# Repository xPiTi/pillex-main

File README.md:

# Pillex

Submission files for MSc project - Pillex - pill dispensing device

Read more at: https://paw3l.com/projects/pillex/

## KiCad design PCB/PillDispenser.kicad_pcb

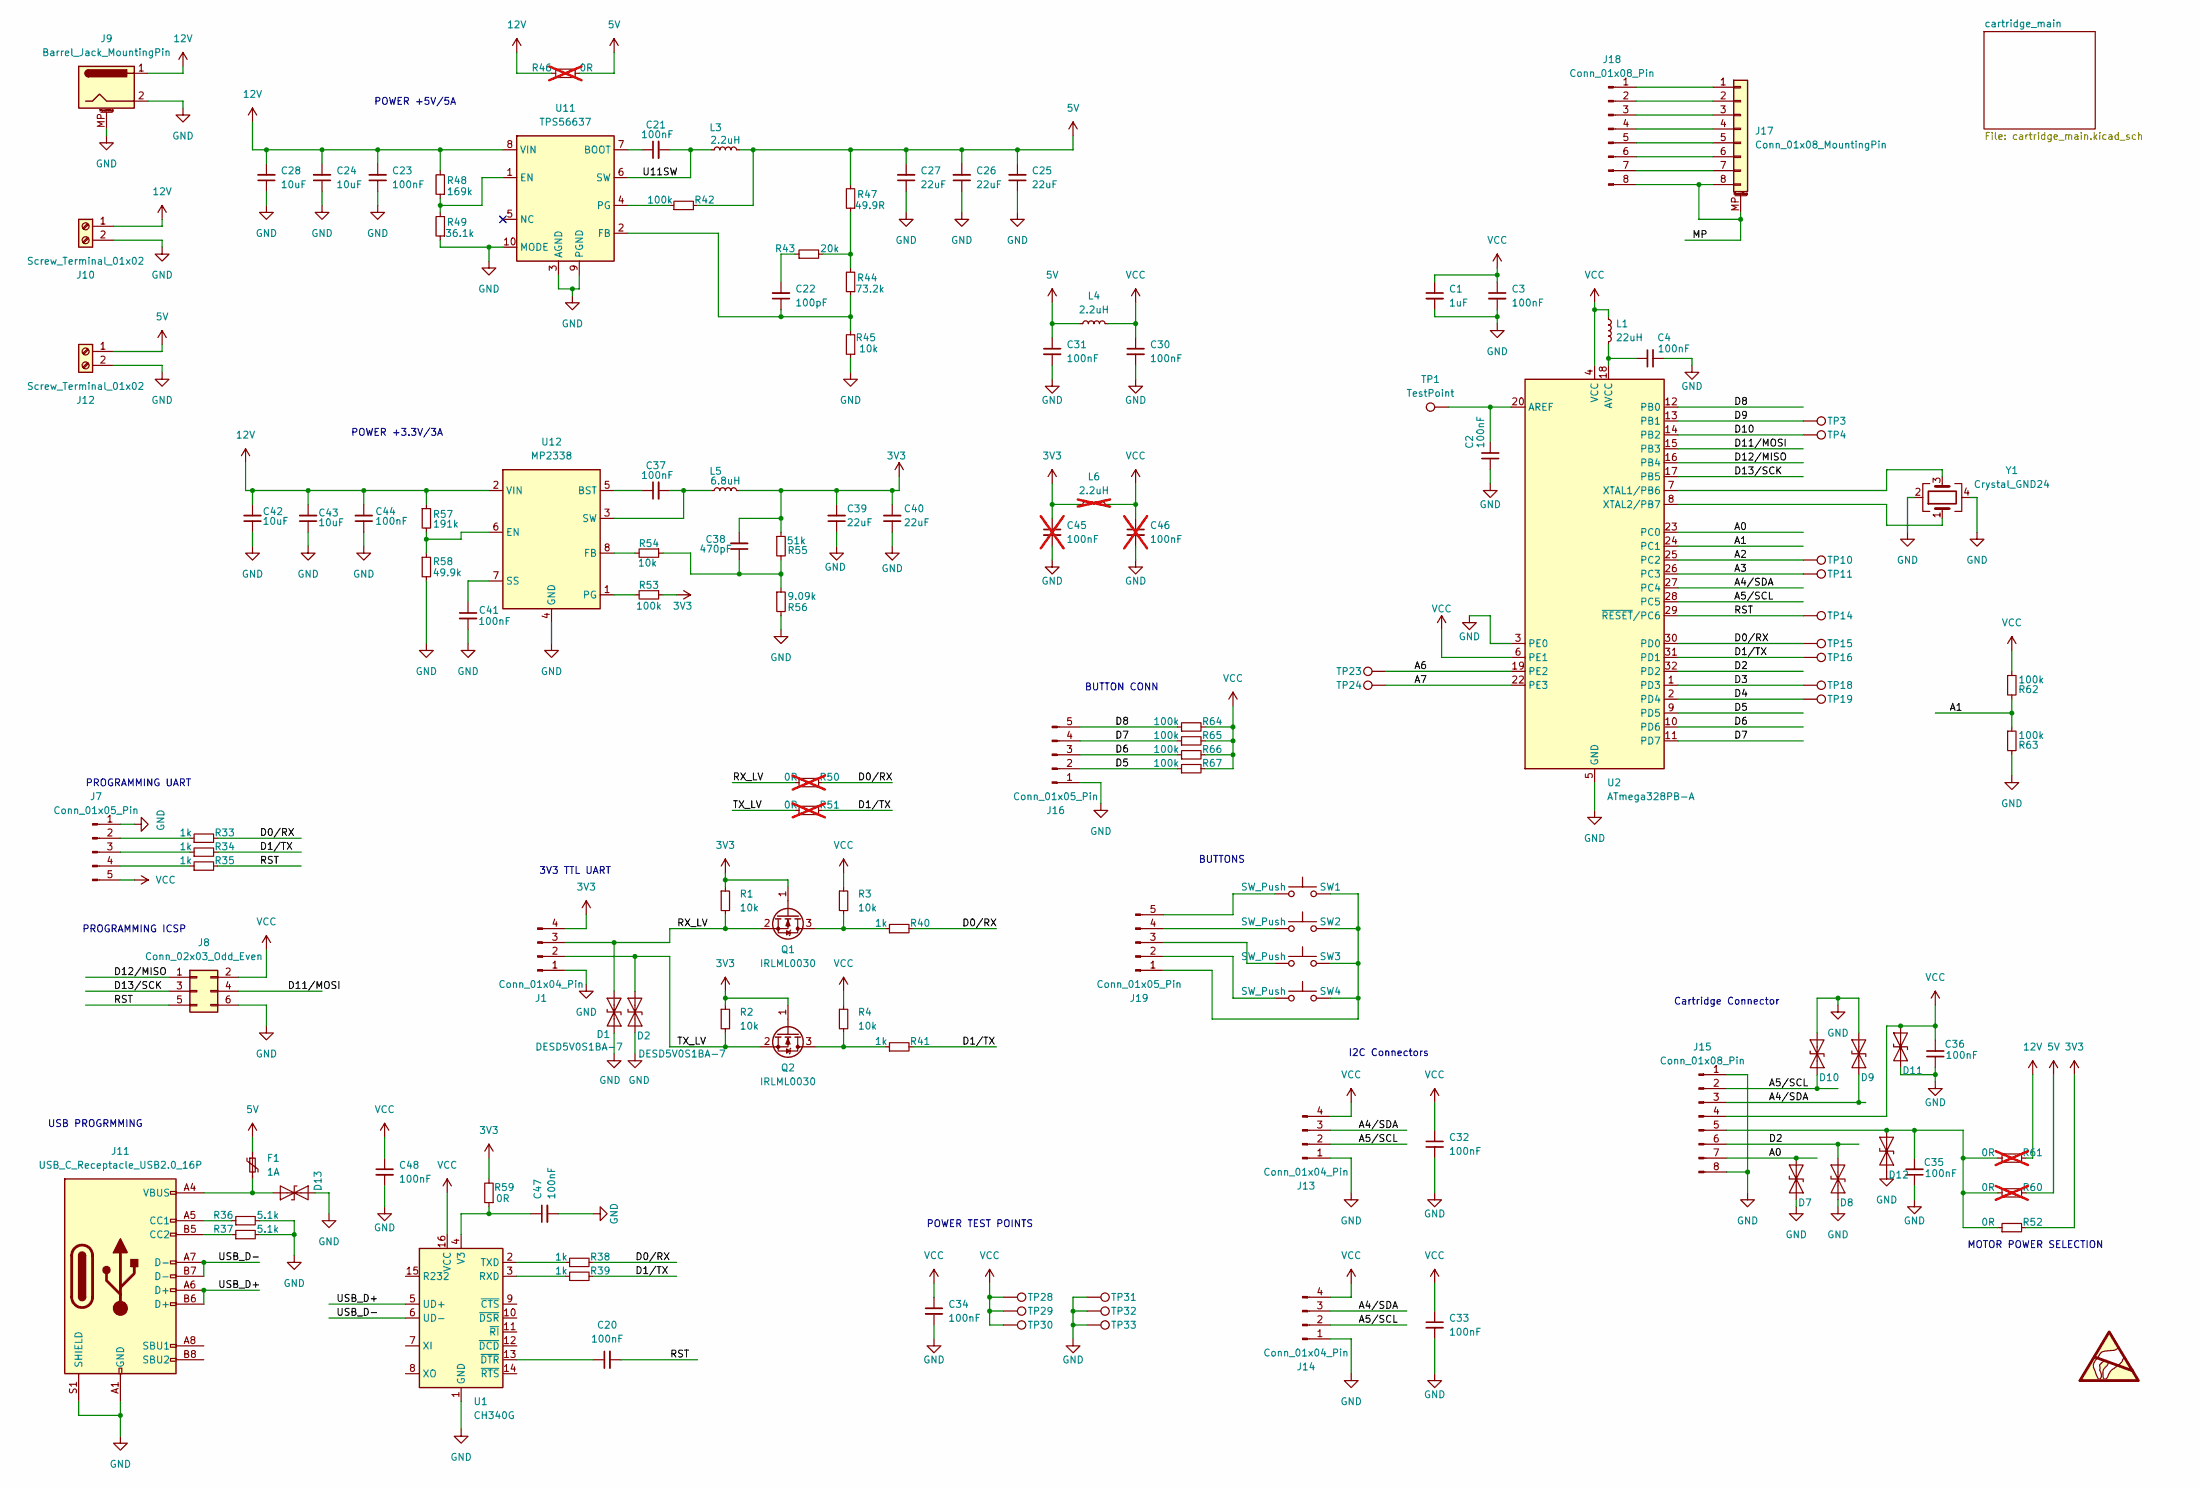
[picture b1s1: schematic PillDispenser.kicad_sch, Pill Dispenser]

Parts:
C1: 1uF; C_0805_2012Metric_Pad1.18x1.45mm_HandSolder
C2, C3, C4, C20, C21, C23, C30, C31, C32, C33, C34, C35, C36, C37, C41, C44, C47, C48: 100nF; C_0805_2012Metric_Pad1.18x1.45mm_HandSolder
C22: 100pF; C_0805_2012Metric_Pad1.18x1.45mm_HandSolder
C24, C28, C42, C43: 10uF; C_0805_2012Metric_Pad1.18x1.45mm_HandSolder
C25, C26, C27, C39, C40: 22uF; C_1206_3216Metric_Pad1.33x1.80mm_HandSolder
C38: 470pF; C_0805_2012Metric_Pad1.18x1.45mm_HandSolder
C45, C46: 100nF; C_0805_2012Metric_Pad1.18x1.45mm_HandSolder; not fitted
D1, D2, D7, D8, D9, D10, D11, D12, D13: DESD5V0S1BA-7; D_SOD-323
F1: 1A; D_1206_3216Metric_Pad1.42x1.75mm_HandSolder
J1, J13, J14: Conn_01x04_Pin; PinHeader_1x04_P2.54mm_Vertical
J7, J16, J19: Conn_01x05_Pin; PinHeader_1x05_P2.54mm_Vertical
J8: Conn_02x03_Odd_Even; PinHeader_2x03_P2.54mm_Vertical
J9: Barrel_Jack_MountingPin; BarrelJack_CUI_PJ-063AH_Horizontal
J10, J12: Screw_Terminal_01x02; Altech_AK100_1x02_P5.00mm
J11: USB_C_Receptacle_USB2.0_16P; USB_C_Receptacle_GCT_USB4085
J15, J18: Conn_01x08_Pin; PinHeader_1x08_P2.54mm_Vertical
J17: Conn_01x08_MountingPin; 009155008852006
L1: 22uH; L_0805_2012Metric_Pad1.15x1.40mm_HandSolder
L3: 2.2uH; L_Coilcraft_XAL4030-XXX
L4: 2.2uH; L_0805_2012Metric_Pad1.15x1.40mm_HandSolder
L5: 6.8uH; L_Coilcraft_XAL4030-XXX
L6: 2.2uH; L_0805_2012Metric_Pad1.15x1.40mm_HandSolder; not fitted
Q1, Q2: IRLML0030; SOT-23
R1, R2, R3, R4, R45, R54: 10k; R_0603_1608Metric_Pad0.98x0.95mm_HandSolder
R33, R34, R35, R38, R39, R40, R41: 1k; R_0603_1608Metric_Pad0.98x0.95mm_HandSolder
R36, R37: 5.1k; R_0603_1608Metric_Pad0.98x0.95mm_HandSolder
R42, R53, R62, R63, R64, R65, R66, R67: 100k; R_0603_1608Metric_Pad0.98x0.95mm_HandSolder
R43: 20k; R_0603_1608Metric_Pad0.98x0.95mm_HandSolder
R44: 73.2k; R_0603_1608Metric_Pad0.98x0.95mm_HandSolder
R46, R50, R51, R60, R61: 0R; R_0603_1608Metric_Pad0.98x0.95mm_HandSolder; not fitted
R47: 49.9R; R_0603_1608Metric_Pad0.98x0.95mm_HandSolder
R48: 169k; R_0603_1608Metric_Pad0.98x0.95mm_HandSolder
R49: 36.1k; R_0603_1608Metric_Pad0.98x0.95mm_HandSolder
R52, R59: 0R; R_0603_1608Metric_Pad0.98x0.95mm_HandSolder
R55: 51k; R_0603_1608Metric_Pad0.98x0.95mm_HandSolder
R56: 9.09k; R_0603_1608Metric_Pad0.98x0.95mm_HandSolder
R57: 191k; R_0603_1608Metric_Pad0.98x0.95mm_HandSolder
R58: 49.9k; R_0603_1608Metric_Pad0.98x0.95mm_HandSolder
SW1, SW2, SW3, SW4: SW_Push; SW_PUSH_6mm_H5mm
TP1, TP3, TP4, TP10, TP11, TP14, TP15, TP16, TP18, TP19, TP23, TP24, TP28, TP29, TP30, TP31, TP32, TP33: TestPoint; TestPoint_Pad_D1.5mm_3D_Model
U1: CH340G; SOIC-16_3.9x9.9mm_P1.27mm
U2: ATmega328PB-A; TQFP-32_7x7mm_P0.8mm
U11: TPS56637; Texas_VQFN-HR_3.1x3.1mm_P1mm_RPA0010A
U12: MP2338; SOT-583-8
Y1: Crystal_GND24; Crystal_SMD_Abracon_ABM8G-4Pin_3.2x2.5mm

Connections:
3V3: C38.2, C39.2, C40.2, C45.1, J1.4, L5.2, L6.1, Q1.1 (G), Q2.1 (G), R1.1, R2.1, R52.2, R53.1, R55.1, R59.2
5V: C25.2, C26.2, C27.2, C31.1, F1.1, J12.1, L3.2, L4.1, R42.2, R46.2, R47.2, R60.2
12V: C23.2, C24.2, C28.2, C42.2, C43.2, C44.2, J9.1, J10.1, R46.1, R48.2, R57.1, R61.2, U11.8 (VIN), U12.2 (VIN)
/A0: D7.2 (A2), J15.7, U2.23 (PC0)
/A1: R62.2, R63.1, U2.24 (PC1)
/A2: TP10.1, U2.25 (PC2)
/A3: TP11.1, U2.26 (PC3)
/A4/SDA: D9.1 (A1), J13.3, J14.3, J15.3, U2.27 (PC4)
/A5/SCL: D10.1 (A1), J13.2, J14.2, J15.2, U2.28 (PC5)
/A6: TP23.1, U2.19 (PE2)
/A7: TP24.1, U2.22 (PE3)
/D0/RX: R33.2, R38.2, R40.2, R50.2, TP15.1, U2.30 (PD0)
/D1/TX: R34.2, R39.2, R41.2, R51.2, TP16.1, U2.31 (PD1)
/D2: D8.2 (A2), J15.6, U2.32 (PD2)
/D3: TP18.1, U2.1 (PD3)
/D4: TP19.1, U2.2 (PD4)
/D5: J16.2, R67.1, U2.9 (PD5)
/D6: J16.3, R66.1, U2.10 (PD6)
/D7: J16.4, R65.1, U2.11 (PD7)
/D8: J16.5, R64.1, U2.12 (PB0)
/D9: TP3.1, U2.13 (PB1)
/D10: TP4.1, U2.14 (PB2)
/D11/MOSI: J8.4, U2.15 (PB3)
/D12/MISO: J8.1, U2.16 (PB4)
/D13/SCK: J8.3, U2.17 (PB5)
/MP: J17.8, J17.MP (MountPin), J18.8
/RST: C20.2, J8.5, R35.2, TP14.1, U2.29 (~RESET/PC6)
/RX_LV: D1.2 (A2), J1.3, Q1.2 (S), R1.2, R50.1
/TX_LV: D2.2 (A2), J1.2, Q2.2 (S), R2.2, R51.1
/U11SW: C21.2, L3.1, U11.6 (SW)
/USB_D+: J11.A6 (D+), J11.B6 (D+), U1.5 (UD+)
/USB_D-: J11.A7 (D-), J11.B7 (D-), U1.6 (UD-)
GND: C1.2, C2.1, C3.2, C4.2, C23.1, C24.1, C25.1, C26.1, C27.1, C28.1, C30.2, C31.2, C32.2, C33.2, C34.2, C35.1, C36.1, C39.1, C40.1, C41.2, C42.1, C43.1, C44.1, C45.2, C46.2, C47.2, C48.2, D1.1 (A1), D2.1 (A1), D7.1 (A1), D8.1 (A1), D9.2 (A2), D10.2 (A2), D11.1 (A1), D12.1 (A1), D13.1 (A1), J1.1, J7.1, J8.6, J9.2, J9.MP (MountPin), J10.2, J11.A1 (GND), J11.A12 (GND), J11.B1 (GND), J11.B12 (GND), J11.S1 (SHIELD), J12.2, J13.1, J14.1, J15.1, J15.8, J16.1, R36.2, R37.2, R45.1, R49.1, R56.2, R58.2, R63.2, TP31.1, TP32.1, TP33.1, U1.1 (GND), U2.3 (PE0), U2.5 (GND), U2.21 (GND), U11.3 (AGND), U11.9 (PGND), U11.10 (MODE), U12.4 (GND), Y1.2, Y1.4
unnamed: C22.2, R43.1
unnamed: C38.1, R54.1, R55.2, R56.1
unnamed: C35.2, D12.2 (A2), J15.5, R52.1, R60.1, R61.1
unnamed: D13.2 (A2), F1.2, J11.A4 (VBUS), J11.A9 (VBUS), J11.B4 (VBUS), J11.B9 (VBUS)
unnamed: J7.2, R33.1
unnamed: J7.3, R34.1
unnamed: J7.4, R35.1
unnamed: J11.A5 (CC1), R36.1
unnamed: J11.B5 (CC2), R37.1
unnamed: J17.1, J18.1
unnamed: J17.2, J18.2
unnamed: J17.3, J18.3
unnamed: J17.4, J18.4
unnamed: J17.5, J18.5
unnamed: J17.6, J18.6
unnamed: J17.7, J18.7
unnamed: J19.1, SW1.2, SW2.2, SW3.2, SW4.2
unnamed: J19.2, SW4.1
unnamed: J19.3, SW3.1
unnamed: J19.4, SW2.1
unnamed: J19.5, SW1.1
unnamed: Q1.3 (D), R3.2, R40.1
unnamed: Q2.3 (D), R4.2, R41.1
unnamed: R43.2, R44.2, R47.1
unnamed: R39.1, U1.3 (RXD)
unnamed: R38.1, U1.2 (TXD)
unnamed: C47.1, R59.1, U1.4 (V3)
unnamed: C20.1, U1.13 (~DTR)
unnamed: C2.2, TP1.1, U2.20 (AREF)
unnamed: C4.1, L1.2, U2.18 (AVCC)
unnamed: U2.7 (XTAL1/PB6), Y1.3
unnamed: U2.8 (XTAL2/PB7), Y1.1
unnamed: C21.1, U11.7 (BOOT)
unnamed: R48.1, R49.2, U11.1 (EN)
unnamed: C22.1, R44.1, R45.2, U11.2 (FB)
unnamed: R42.1, U11.4 (PG)
unnamed: C37.1, U12.5 (BST)
unnamed: R57.2, R58.1, U12.6 (EN)
unnamed: R54.2, U12.8 (FB)
unnamed: R53.2, U12.1 (PG)
unnamed: C41.1, U12.7 (SS)
unnamed: C37.2, L5.1, U12.3 (SW)
VCC: C1.1, C3.1, C30.1, C32.1, C33.1, C34.1, C36.2, C46.1, C48.1, D11.2 (A2), J7.5, J8.2, J13.4, J14.4, J15.4, L1.1, L4.2, L6.2, R3.1, R4.1, R62.1, R64.2, R65.2, R66.2, R67.2, TP28.1, TP29.1, TP30.1, U1.16 (VCC), U2.4 (VCC), U2.6 (PE1)

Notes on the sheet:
PROGRAMMING UART
BUTTON CONN
BUTTONS
I2C Connectors
Cartridge Connector
MOTOR POWER SELECTION
POWER +3.3V/3A
POWER TEST POINTS
USB PROGRMMING
POWER +5V/5A
3V3 TTL UART
PROGRAMMING ICSP

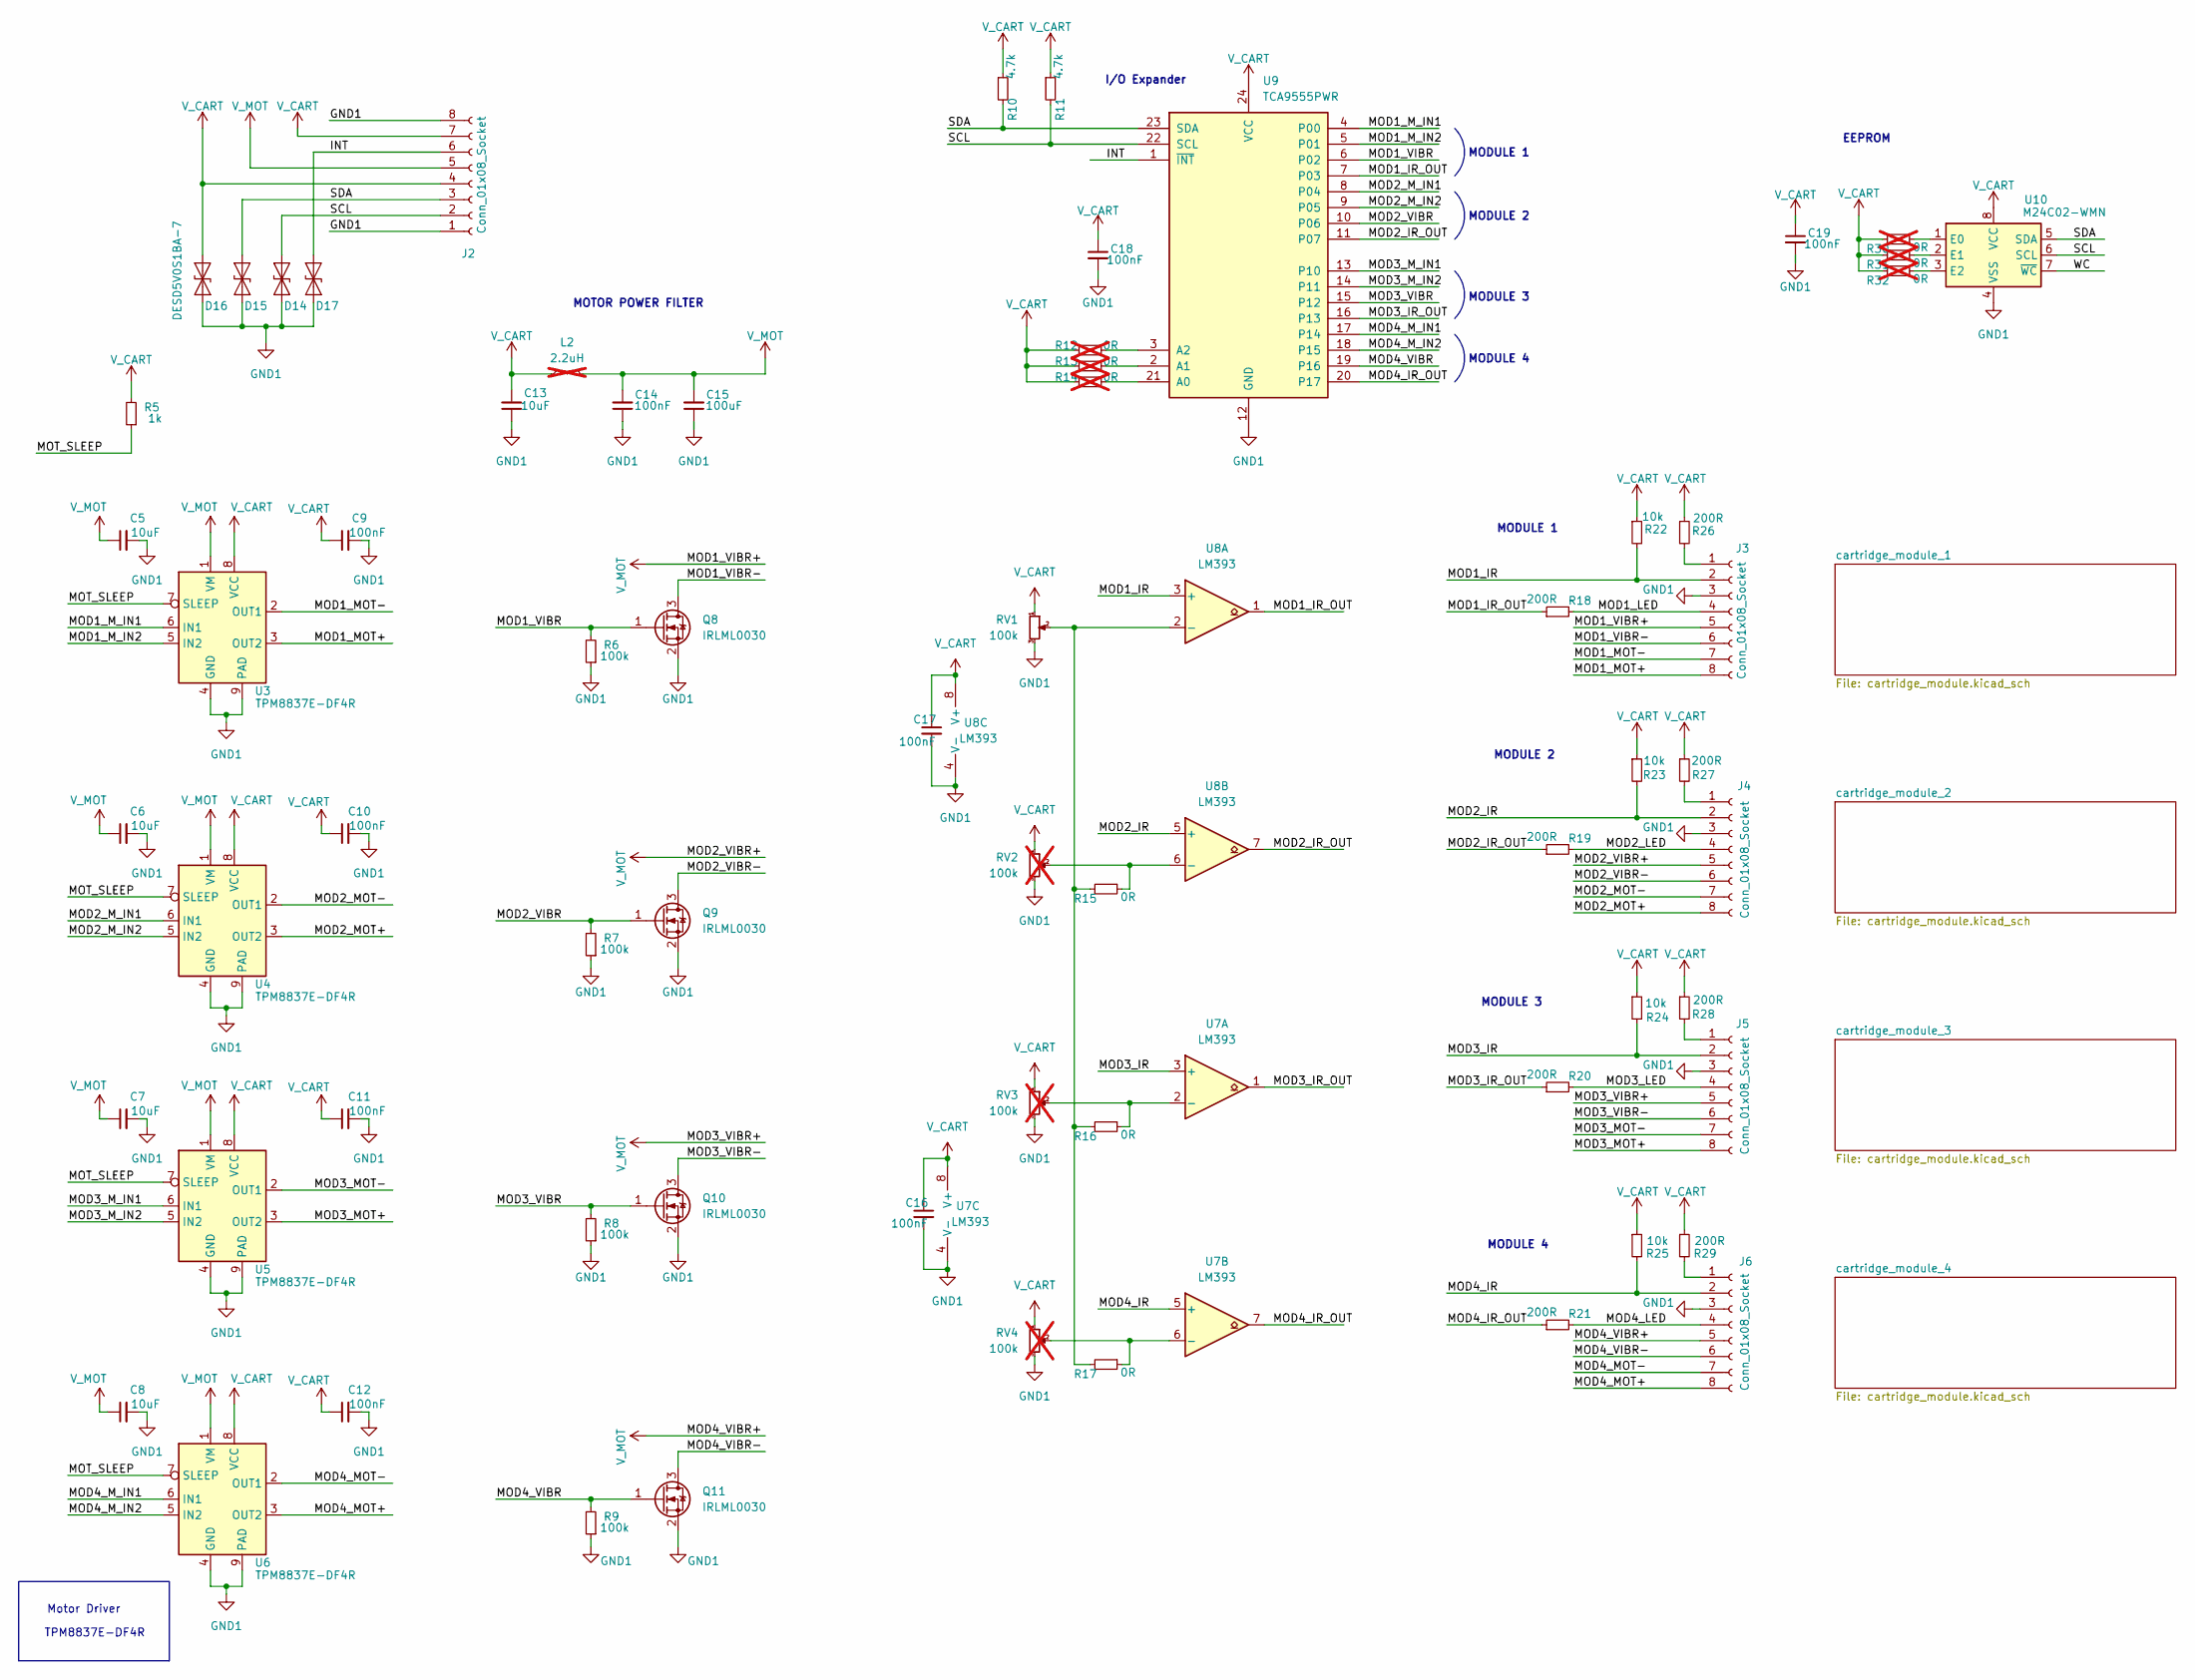
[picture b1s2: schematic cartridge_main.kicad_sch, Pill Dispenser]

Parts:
C5, C6, C7, C8, C13: 10uF; C_0805_2012Metric_Pad1.18x1.45mm_HandSolder
C9, C10, C11, C12, C14, C16, C17, C18, C19: 100nF; C_0805_2012Metric_Pad1.18x1.45mm_HandSolder
C15: 100uF; C_1206_3216Metric_Pad1.33x1.80mm_HandSolder
D14, D15, D16, D17: DESD5V0S1BA-7; D_SOD-323
J2: Conn_01x08_Socket; PCB_Contacts_8pin
J3, J4, J5, J6: Conn_01x08_Socket; PinSocket_1x08_P1.27mm_Vertical
L2: 2.2uH; L_1210_3225Metric_Pad1.42x2.65mm_HandSolder; not fitted
Q8, Q9, Q10, Q11: IRLML0030; SOT-23
R5: 1k; R_0603_1608Metric_Pad0.98x0.95mm_HandSolder
R6, R7, R8, R9: 100k; R_0603_1608Metric_Pad0.98x0.95mm_HandSolder
R10, R11: 4.7k; R_0603_1608Metric_Pad0.98x0.95mm_HandSolder
R12, R13, R14, R30, R31, R32: 0R; R_0603_1608Metric_Pad0.98x0.95mm_HandSolder; not fitted
R15, R16, R17: 0R; R_0603_1608Metric_Pad0.98x0.95mm_HandSolder
R18, R19, R20, R21, R26, R27, R28, R29: 200R; R_0603_1608Metric_Pad0.98x0.95mm_HandSolder
R22, R23, R24, R25: 10k; R_0603_1608Metric_Pad0.98x0.95mm_HandSolder
RV1: 100k; Potentiometer_Bourns_TC33X_Vertical
RV2, RV3, RV4: 100k; Potentiometer_Bourns_TC33X_Vertical; not fitted
U3, U4, U5, U6: TPM8837E-DF4R; DFN-8-1EP_2x2mm_P0.5mm_EP1.05x1.75mm_hand_solder
U7, U8: LM393; SOIC-8_3.9x4.9mm_P1.27mm
U9: TCA9555PWR; TSSOP-24_4.4x7.8mm_P0.65mm
U10: M24C02-WMN; SOIC-8_3.9x4.9mm_P1.27mm

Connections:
/cartridge_main/INT: D17.2 (A2), J2.6, U9.1 (~INT)
/cartridge_main/MOD1_IR: J3.2, R22.2, U8.3 (+)
/cartridge_main/MOD1_IR_OUT: R18.1, U8.1, U9.7 (P03)
/cartridge_main/MOD1_LED: J3.4, R18.2
/cartridge_main/MOD1_MOT+: J3.8, U3.3 (OUT2)
/cartridge_main/MOD1_MOT-: J3.7, U3.2 (OUT1)
/cartridge_main/MOD1_M_IN1: U3.6 (IN1), U9.4 (P00)
/cartridge_main/MOD1_M_IN2: U3.5 (IN2), U9.5 (P01)
/cartridge_main/MOD1_VIBR: Q8.1 (G), R6.2, U9.6 (P02)
/cartridge_main/MOD1_VIBR-: J3.6, Q8.3 (D)
/cartridge_main/MOD2_IR: J4.2, R23.2, U8.5 (+)
/cartridge_main/MOD2_IR_OUT: R19.1, U8.7, U9.11 (P07)
/cartridge_main/MOD2_LED: J4.4, R19.2
/cartridge_main/MOD2_MOT+: J4.8, U4.3 (OUT2)
/cartridge_main/MOD2_MOT-: J4.7, U4.2 (OUT1)
/cartridge_main/MOD2_M_IN1: U4.6 (IN1), U9.8 (P04)
/cartridge_main/MOD2_M_IN2: U4.5 (IN2), U9.9 (P05)
/cartridge_main/MOD2_VIBR: Q9.1 (G), R7.2, U9.10 (P06)
/cartridge_main/MOD2_VIBR-: J4.6, Q9.3 (D)
/cartridge_main/MOD3_IR: J5.2, R24.2, U7.3 (+)
/cartridge_main/MOD3_IR_OUT: R20.1, U7.1, U9.16 (P13)
/cartridge_main/MOD3_LED: J5.4, R20.2
/cartridge_main/MOD3_MOT+: J5.8, U5.3 (OUT2)
/cartridge_main/MOD3_MOT-: J5.7, U5.2 (OUT1)
/cartridge_main/MOD3_M_IN1: U5.6 (IN1), U9.13 (P10)
/cartridge_main/MOD3_M_IN2: U5.5 (IN2), U9.14 (P11)
/cartridge_main/MOD3_VIBR: Q10.1 (G), R8.2, U9.15 (P12)
/cartridge_main/MOD3_VIBR-: J5.6, Q10.3 (D)
/cartridge_main/MOD4_IR: J6.2, R25.2, U7.5 (+)
/cartridge_main/MOD4_IR_OUT: R21.1, U7.7, U9.20 (P17)
/cartridge_main/MOD4_LED: J6.4, R21.2
/cartridge_main/MOD4_MOT+: J6.8, U6.3 (OUT2)
/cartridge_main/MOD4_MOT-: J6.7, U6.2 (OUT1)
/cartridge_main/MOD4_M_IN1: U6.6 (IN1), U9.17 (P14)
/cartridge_main/MOD4_M_IN2: U6.5 (IN2), U9.18 (P15)
/cartridge_main/MOD4_VIBR: Q11.1 (G), R9.2, U9.19 (P16)
/cartridge_main/MOD4_VIBR-: J6.6, Q11.3 (D)
/cartridge_main/MOT_SLEEP: R5.1, U3.7 (SLEEP), U4.7 (SLEEP), U5.7 (SLEEP), U6.7 (SLEEP)
/cartridge_main/SCL: D14.2 (A2), J2.2, R11.2, U9.22 (SCL), U10.6 (SCL)
/cartridge_main/SDA: D15.2 (A2), J2.3, R10.2, U9.23 (SDA), U10.5 (SDA)
/cartridge_main/WC: U10.7 (~WC)
GND1: C5.2, C6.2, C7.2, C8.2, C9.2, C10.2, C11.2, C12.2, C13.1, C14.1, C15.1, C16.2, C17.2, C18.2, C19.2, D14.1 (A1), D15.1 (A1), D16.1 (A1), D17.1 (A1), J2.1, J2.8, J3.3, J4.3, J5.3, J6.3, Q8.2 (S), Q9.2 (S), Q10.2 (S), Q11.2 (S), R6.1, R7.1, R8.1, R9.1, RV1.3, RV2.3, RV3.3, RV4.3, U3.4 (GND), U3.9 (PAD), U4.4 (GND), U4.9 (PAD), U5.4 (GND), U5.9 (PAD), U6.4 (GND), U6.9 (PAD), U7.4 (V-), U8.4 (V-), U9.12 (GND), U10.4 (VSS)
unnamed: J3.1, R26.2
unnamed: J4.1, R27.2
unnamed: J5.1, R28.2
unnamed: J6.1, R29.2
unnamed: R16.1, RV3.2, U7.2 (-)
unnamed: R17.1, RV4.2, U7.6 (-)
unnamed: R15.2, R16.2, R17.2, RV1.2, U8.2 (-)
unnamed: R15.1, RV2.2, U8.6 (-)
unnamed: R14.1, U9.21 (A0)
unnamed: R13.1, U9.2 (A1)
unnamed: R12.1, U9.3 (A2)
unnamed: R30.1, U10.1 (E0)
unnamed: R31.1, U10.2 (E1)
unnamed: R32.1, U10.3 (E2)
V_CART: C9.1, C10.1, C11.1, C12.1, C13.2, C16.1, C17.1, C18.1, C19.1, D16.2 (A2), J2.4, J2.7, L2.1, R5.2, R10.1, R11.1, R12.2, R13.2, R14.2, R22.1, R23.1, R24.1, R25.1, R26.1, R27.1, R28.1, R29.1, R30.2, R31.2, R32.2, RV1.1, RV2.1, RV3.1, RV4.1, U3.8 (VCC), U4.8 (VCC), U5.8 (VCC), U6.8 (VCC), U7.8 (V+), U8.8 (V+), U9.24 (VCC), U10.8 (VCC)
V_MOT: C5.1, C6.1, C7.1, C8.1, C14.2, C15.2, J2.5, J3.5, J4.5, J5.5, J6.5, L2.2, U3.1 (VM), U4.1 (VM), U5.1 (VM), U6.1 (VM)

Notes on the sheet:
Motor Driver
MODULE 1
TPM8837E-DF4R
MODULE 3
MOTOR POWER FILTER
I/O Expander
MODULE 4
MODULE 2
EEPROM

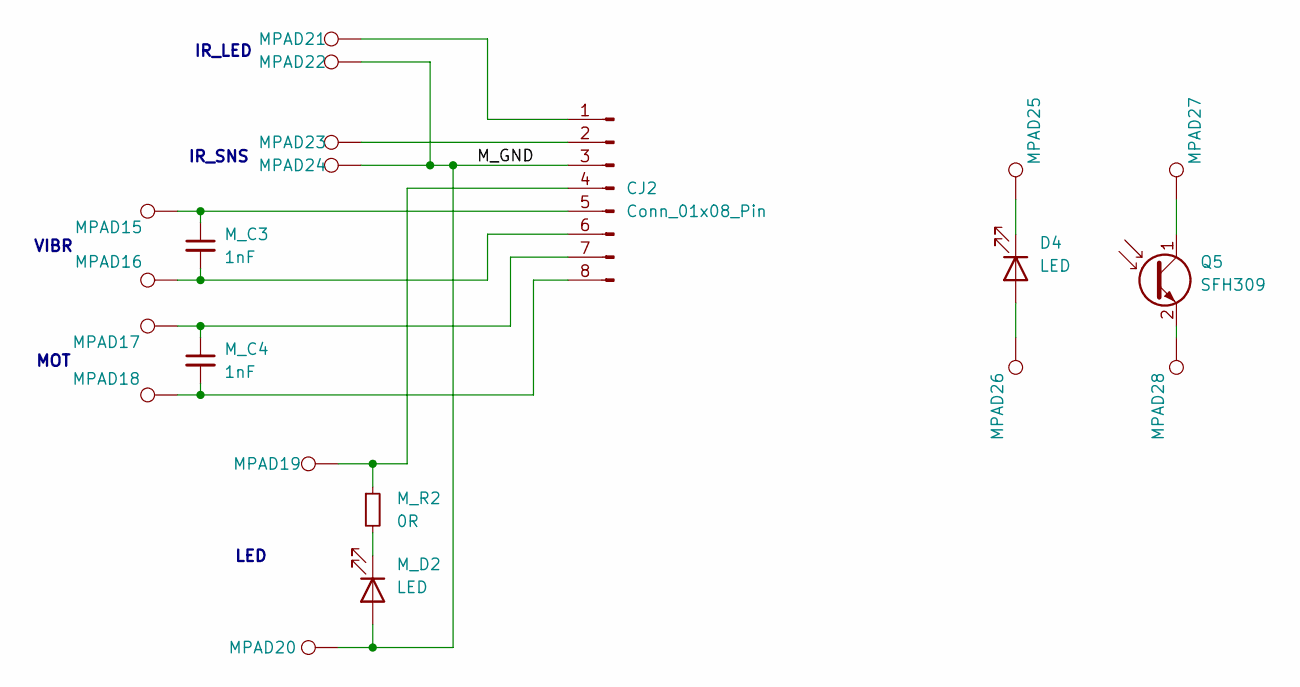
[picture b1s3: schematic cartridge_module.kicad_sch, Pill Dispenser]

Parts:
CJ2: Conn_01x08_Pin; PinHeader_1x08_P1.27mm_Horizontal
D4: LED; LED_D3.0mm_Clear
MPAD15, MPAD16, MPAD17, MPAD18, MPAD19, MPAD20, MPAD21, MPAD22, MPAD23, MPAD24, MPAD25, MPAD26, MPAD27, MPAD28: TestPoint; TestPoint_Pad_D1.5mm_3D_Model
M_C3, M_C4: 1nF; C_0805_2012Metric_Pad1.18x1.45mm_HandSolder
M_D2: LED; LED_0805_2012Metric_Pad1.15x1.40mm_HandSolder
M_R2: 0R; R_0603_1608Metric_Pad0.98x0.95mm_HandSolder
Q5: SFH309; LED_D3.0mm_Clear

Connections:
/cartridge_main/cartridge_module_2/M_GND: CJ2.3, MPAD20.1, MPAD22.1, MPAD24.1, M_D2.2 (A)
unnamed: CJ2.1, MPAD21.1
unnamed: CJ2.2, MPAD23.1
unnamed: CJ2.4, MPAD19.1, M_R2.1
unnamed: CJ2.5, MPAD15.1, M_C3.1
unnamed: CJ2.6, MPAD16.1, M_C3.2
unnamed: CJ2.7, MPAD17.1, M_C4.1
unnamed: CJ2.8, MPAD18.1, M_C4.2
unnamed: D4.2 (A), MPAD26.1
unnamed: D4.1 (K), MPAD25.1
unnamed: M_D2.1 (K), M_R2.2
unnamed: MPAD27.1, Q5.1 (C)
unnamed: MPAD28.1, Q5.2 (E)

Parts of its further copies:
CJ1, CJ3, CJ4: Conn_01x08_Pin; PinHeader_1x08_P1.27mm_Horizontal
D3, D5, D6: LED; LED_D3.0mm_Clear
MPAD1, MPAD2, MPAD3, MPAD4, MPAD5, MPAD6, MPAD7, MPAD8, MPAD9, MPAD10, MPAD11, MPAD12, MPAD13, MPAD14, MPAD29, MPAD30, MPAD31, MPAD32, MPAD33, MPAD34, MPAD35, MPAD36, MPAD37, MPAD38, MPAD39, MPAD40, MPAD41, MPAD42, MPAD43, MPAD44, MPAD45, MPAD46, MPAD47, MPAD48, MPAD49, MPAD50, MPAD51, MPAD52, MPAD53, MPAD54, MPAD55, MPAD56: TestPoint; TestPoint_Pad_D1.5mm_3D_Model
M_C1, M_C2, M_C5, M_C6, M_C7, M_C8: 1nF; C_0805_2012Metric_Pad1.18x1.45mm_HandSolder
M_D1, M_D3, M_D4: LED; LED_0805_2012Metric_Pad1.15x1.40mm_HandSolder
M_R1, M_R3, M_R4: 0R; R_0603_1608Metric_Pad0.98x0.95mm_HandSolder
Q4, Q6, Q7: SFH309; LED_D3.0mm_Clear

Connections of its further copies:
/cartridge_main/cartridge_module_1/M_GND: CJ1.3, MPAD6.1, MPAD8.1, MPAD10.1, M_D1.2 (A)
/cartridge_main/cartridge_module_3/M_GND: CJ3.3, MPAD34.1, MPAD36.1, MPAD38.1, M_D3.2 (A)
/cartridge_main/cartridge_module_4/M_GND: CJ4.3, MPAD48.1, MPAD50.1, MPAD52.1, M_D4.2 (A)
unnamed: CJ1.1, MPAD7.1
unnamed: CJ1.2, MPAD9.1
unnamed: CJ1.4, MPAD5.1, M_R1.1
unnamed: CJ1.5, MPAD1.1, M_C1.1
unnamed: CJ1.6, MPAD2.1, M_C1.2
unnamed: CJ1.7, MPAD3.1, M_C2.1
unnamed: CJ1.8, MPAD4.1, M_C2.2
unnamed: CJ3.1, MPAD35.1
unnamed: CJ3.2, MPAD37.1
unnamed: CJ3.4, MPAD33.1, M_R3.1
unnamed: CJ3.5, MPAD29.1, M_C5.1
unnamed: CJ3.6, MPAD30.1, M_C5.2
unnamed: CJ3.7, MPAD31.1, M_C6.1
unnamed: CJ3.8, MPAD32.1, M_C6.2
unnamed: CJ4.1, MPAD49.1
unnamed: CJ4.2, MPAD51.1
unnamed: CJ4.4, MPAD47.1, M_R4.1
unnamed: CJ4.5, MPAD43.1, M_C7.1
unnamed: CJ4.6, MPAD44.1, M_C7.2
unnamed: CJ4.7, MPAD45.1, M_C8.1
unnamed: CJ4.8, MPAD46.1, M_C8.2
unnamed: D3.2 (A), MPAD12.1
unnamed: D3.1 (K), MPAD11.1
unnamed: D5.2 (A), MPAD40.1
unnamed: D5.1 (K), MPAD39.1
unnamed: D6.2 (A), MPAD54.1
unnamed: D6.1 (K), MPAD53.1
unnamed: M_D1.1 (K), M_R1.2
unnamed: M_D3.1 (K), M_R3.2
unnamed: M_D4.1 (K), M_R4.2
unnamed: MPAD13.1, Q4.1 (C)
unnamed: MPAD14.1, Q4.2 (E)
unnamed: MPAD41.1, Q6.1 (C)
unnamed: MPAD42.1, Q6.2 (E)
unnamed: MPAD55.1, Q7.1 (C)
unnamed: MPAD56.1, Q7.2 (E)

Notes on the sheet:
IR_SNS
IR_LED
VIBR
LED
MOT

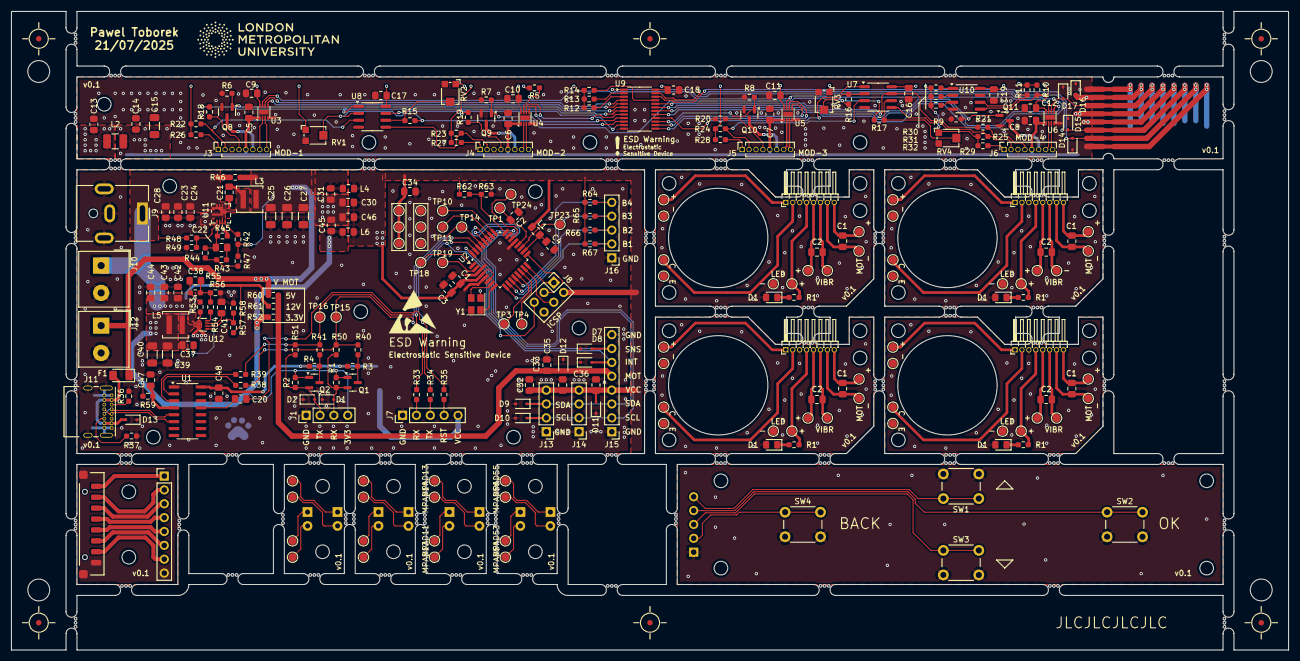
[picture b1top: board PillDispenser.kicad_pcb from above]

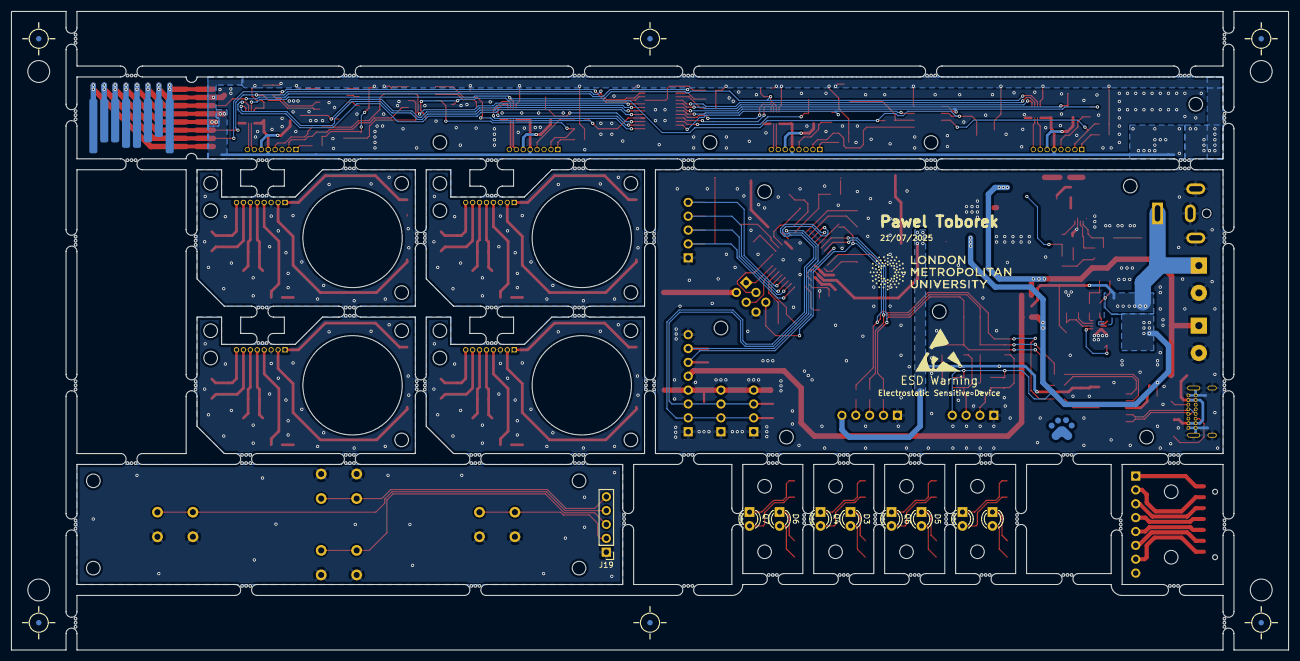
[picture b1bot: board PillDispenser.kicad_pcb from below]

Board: 2 copper layers, 234.0 x 117.0 mm, 350 parts (10 on the bottom side), 185 nets.

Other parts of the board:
mouse-bite-2mm-slot, mouse-bite-2mm-slot#6, mouse-bite-2mm-slot#8, mouse-bite-2mm-slot#9, mouse-bite-2mm-slot#10, mouse-bite-2mm-slot#14, mouse-bite-2mm-slot#22, mouse-bite-2mm-slot#26, mouse-bite-2mm-slot#29, mouse-bite-2mm-slot#34, mouse-bite-2mm-slot#35, mouse-bite-2mm-slot#36, mouse-bite-2mm-slot#40, mouse-bite-2mm-slot#44, mouse-bite-2mm-slot#47, mouse-bite-2mm-slot#49, mouse-bite-2mm-slot#50, mouse-bite-2mm-slot#51, mouse-bite-2mm-slot#52, mouse-bite-2mm-slot#53, mouse-bite-2mm-slot#61, mouse-bite-2mm-slot#62, mouse-bite-2mm-slot#64: VAL**; mouse-bite-2mm-slot
mouse-bite-2mm-slot#2, mouse-bite-2mm-slot#3, mouse-bite-2mm-slot#4, mouse-bite-2mm-slot#5, mouse-bite-2mm-slot#7, mouse-bite-2mm-slot#11, mouse-bite-2mm-slot#12, mouse-bite-2mm-slot#13, mouse-bite-2mm-slot#15, mouse-bite-2mm-slot#16, mouse-bite-2mm-slot#17, mouse-bite-2mm-slot#18, mouse-bite-2mm-slot#19, mouse-bite-2mm-slot#20, mouse-bite-2mm-slot#21, mouse-bite-2mm-slot#23, mouse-bite-2mm-slot#24, mouse-bite-2mm-slot#25, mouse-bite-2mm-slot#27, mouse-bite-2mm-slot#28, mouse-bite-2mm-slot#30, mouse-bite-2mm-slot#31, mouse-bite-2mm-slot#32, mouse-bite-2mm-slot#33, mouse-bite-2mm-slot#37, mouse-bite-2mm-slot#38, mouse-bite-2mm-slot#39, mouse-bite-2mm-slot#41, mouse-bite-2mm-slot#42, mouse-bite-2mm-slot#43, mouse-bite-2mm-slot#45, mouse-bite-2mm-slot#46, mouse-bite-2mm-slot#48, mouse-bite-2mm-slot#54, mouse-bite-2mm-slot#55, mouse-bite-2mm-slot#56, mouse-bite-2mm-slot#57, mouse-bite-2mm-slot#58, mouse-bite-2mm-slot#59, mouse-bite-2mm-slot#60, mouse-bite-2mm-slot#63, mouse-bite-2mm-slot#65, mouse-bite-2mm-slot#66, mouse-bite-2mm-slot#67, mouse-bite-2mm-slot#68: VAL**; mouse-bite-2mm-slot_one_side

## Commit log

2025-11-02 First
2025-11-02 README added
